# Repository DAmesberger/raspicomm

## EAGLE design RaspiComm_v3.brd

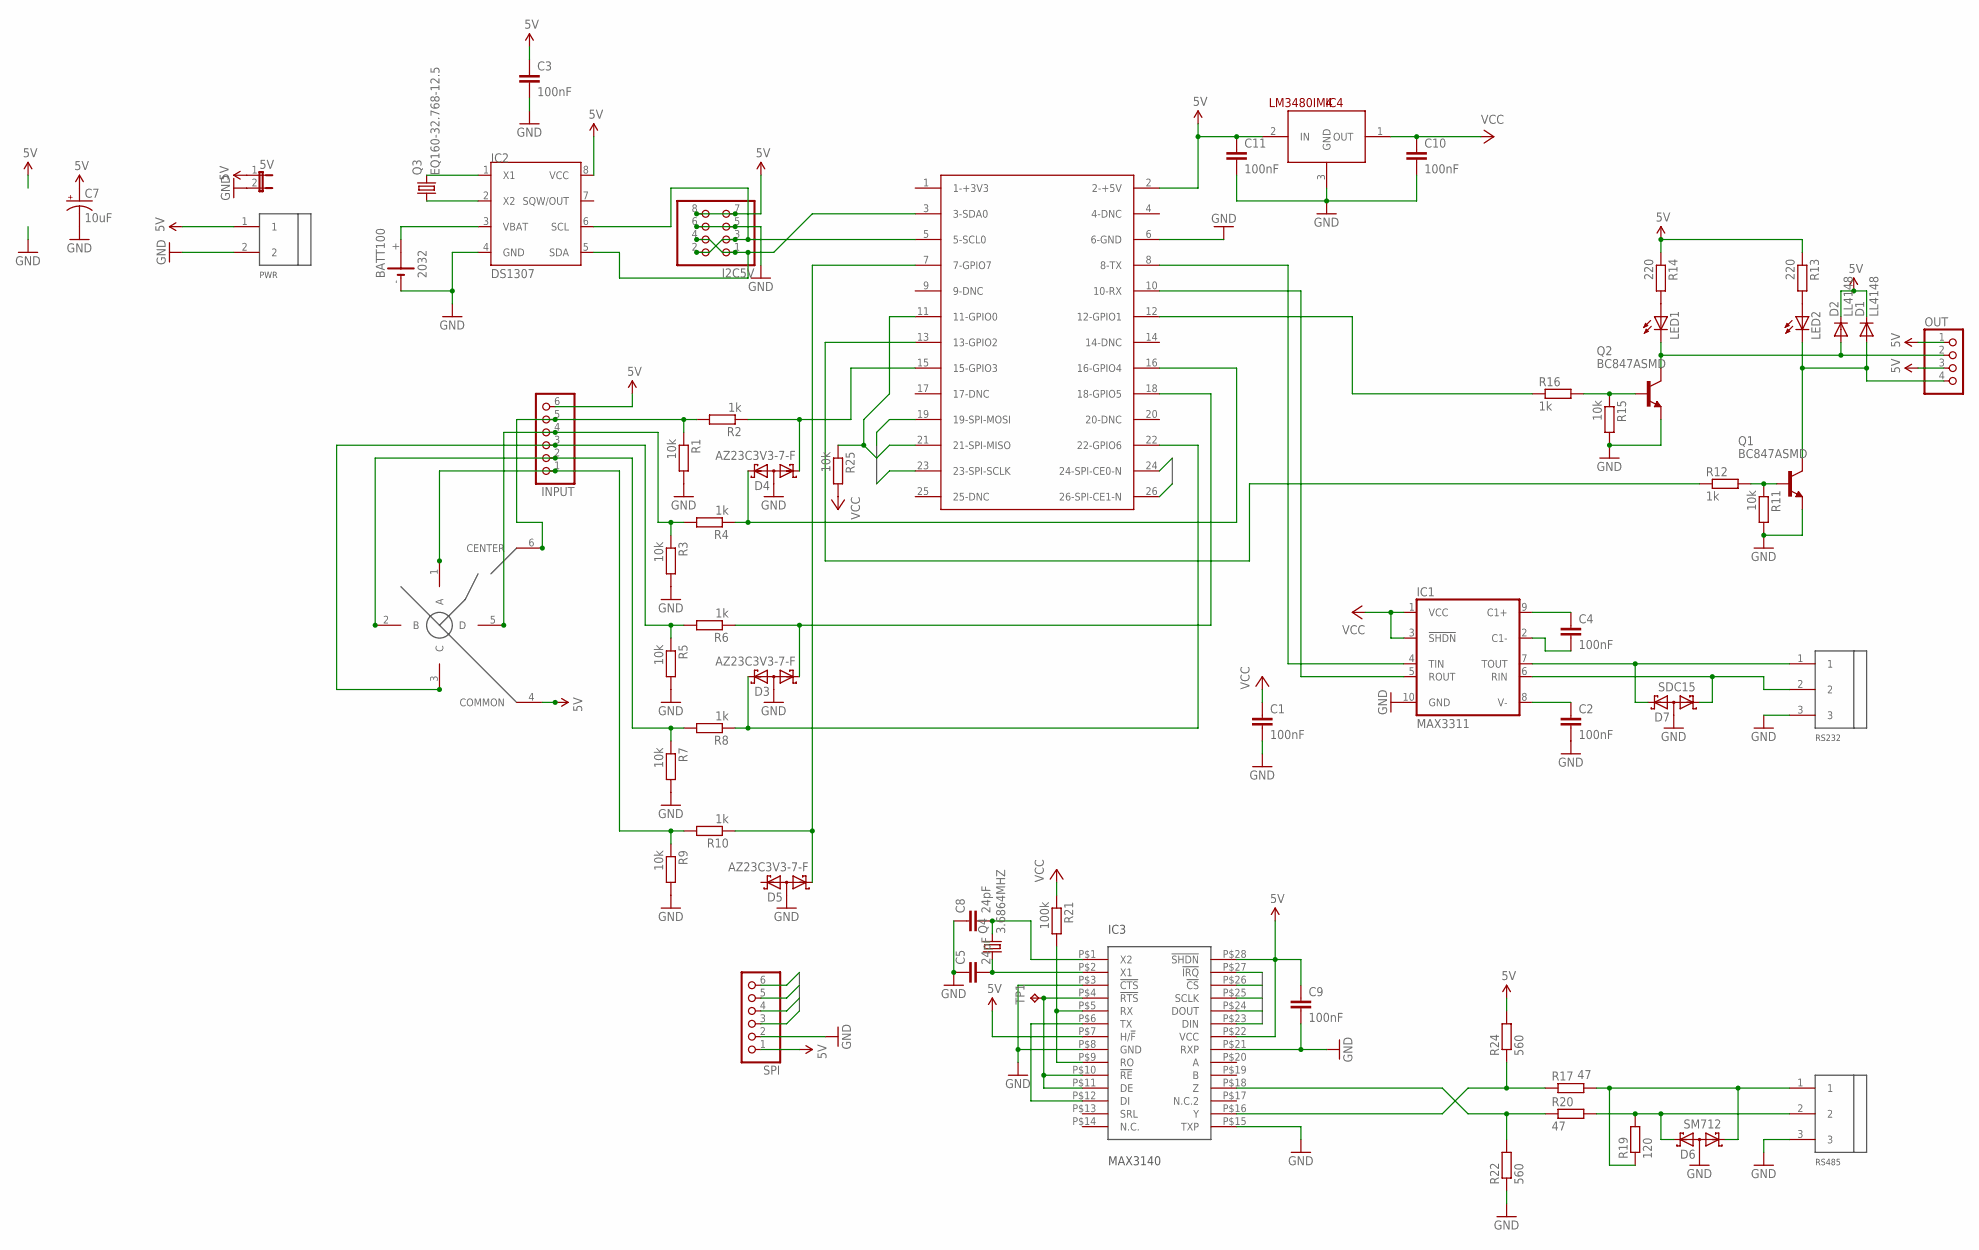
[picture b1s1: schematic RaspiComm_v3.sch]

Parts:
5V: JP1E; JP1
BATT100: 2032; KZH20SMD
C1, C2, C3, C4, C9, C10, C11: 100nF; C0603
C5, C8: 24pF; C0603
C7: 10uF; B(3528-21)
D1, D2: LL4148; SOD80C
D3, D4, D5: AZ23C3V3-7-F; SOT23
D6: SM712; SOT23
D7: SDC15; SOT23
I2C5V: PINHD-2X4_2.54-SMD; 2X04SMD
IC1: MAX3311; UMAX10
IC2: DS1307; SOIC-8
IC3: MAX3140; QSOP28
IC4: LM3480IM4; SOT23-3
INPUT: PINHD-1X6_2.00; 1X06M
LED1, LED2: LEDSML0805; SML0805
OUT: PINHD-1X4_2.00; 1X04M
PWR: 31182102
Q1, Q2: BC847ASMD; SOT23
Q3: EQ160-32.768-12.5; EQ160
Q4: 3.6864MHZ; 49USMX
R1, R3, R5, R7, R9, R11, R15, R25: 10k; R0603
R2, R4, R6, R8, R10, R12, R16: 1k; R0603
R13, R14: 220; R0603
R17, R20: 47; R1206
R19: 120; R1206
R21: 100k; R0603
R22, R24: 560; R0603
RS232, RS485: 31182103
SPI: PINHD-1X6_2.00; 1X06M
SW1: SKQUDBE010; SKQU-SMD
TP1: TPB1,27; B1,27
U$7: RASPBERRY-PIHEADER; RASPI_GPIO_HEADER

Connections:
5V: 5V.1, C3.1, C7.+, C9.1, C11.1, D1.C, D2.C, I2C5V.7, I2C5V.8, IC2.8 (VCC), IC3.P$7 (H/!F), IC3.P$22 (VCC), IC3.P$28 (!SHDN), IC4.2 (IN), INPUT.6, OUT.1, OUT.3, PWR.1, R13.1, R14.1, R24.2, SPI.1, SW1.4 (COMMON), U$7.2 (2-+5V)
CS1: IC3.P$26 (!CS), U$7.24 (24-SPI-CE0-N)
CS2: SPI.3, U$7.26 (26-SPI-CE1-N)
GND: 5V.2, BATT100.-, C1.2, C2.2, C3.2, C5.1, C7.-, C8.1, C9.2, C10.2, C11.2, D3.3 (AA), D4.3 (AA), D5.3 (AA), D6.3 (AA), D7.3 (AA), I2C5V.5, I2C5V.6, IC1.10 (GND), IC2.4 (GND), IC3.P$3 (!CTS), IC3.P$8 (GND), IC3.P$15 (TXP), IC3.P$21 (RXP), IC4.3 (GND), PWR.2, Q1.2 (E), Q2.2 (E), R1.2, R3.2, R5.2, R7.2, R9.2, R11.2, R15.2, R22.1, RS232.3, RS485.3, SPI.2, U$7.6 (6-GND)
IRQ: IC3.P$27 (!IRQ), R25.1, U$7.11 (11-GPIO0)
MISO: IC3.P$24 (DOUT), SPI.5, U$7.21 (21-SPI-MISO)
MOSI: IC3.P$23 (DIN), SPI.6, U$7.19 (19-SPI-MOSI)
unnamed: R16.1, U$7.12 (12-GPIO1)
unnamed: C5.2, IC3.P$2 (X1), Q4.P$1 (1)
unnamed: IC3.P$5 (RX), IC3.P$9 (RO), R21.2
unnamed: IC2.1 (X1), Q3.P$2 (2)
unnamed: IC3.P$16 (Y), R17.1, R24.1
unnamed: IC3.P$18 (Z), R20.1, R22.2
unnamed: I2C5V.2, I2C5V.3, IC2.6 (SCL), U$7.5 (5-SCL0)
unnamed: INPUT.5, R1.1, R2.2, SW1.6 (CENTER)
unnamed: IC3.P$4 (!RTS), IC3.P$10 (!RE), IC3.P$11 (DE), TP1.TP
unnamed: INPUT.4, R3.1, R4.2, SW1.5 (D)
unnamed: INPUT.3, R5.1, R6.2, SW1.3 (C)
unnamed: INPUT.2, R7.1, R8.2, SW1.2 (B)
unnamed: INPUT.1, R9.1, R10.2, SW1.1 (A)
unnamed: D4.1 (K1), R2.1, U$7.15 (15-GPIO3)
unnamed: D4.2 (K2), R4.1, U$7.16 (16-GPIO4)
unnamed: D3.1 (K1), R6.1, U$7.18 (18-GPIO5)
unnamed: D3.2 (K2), R8.1, U$7.22 (22-GPIO6)
unnamed: D5.1 (K1), R10.1, U$7.7 (7-GPIO7)
unnamed: D6.2 (K2), R19.2, R20.2, RS485.2
unnamed: C2.1, IC1.8 (V-)
unnamed: C4.2, IC1.2 (C1-)
unnamed: C4.1, IC1.9 (C1+)
unnamed: D6.1 (K1), R17.2, R19.1, RS485.1
unnamed: LED1.A, R14.2
unnamed: D7.2 (K2), IC1.7 (TOUT), RS232.1
unnamed: D7.1 (K1), IC1.6 (RIN), RS232.2
unnamed: C8.2, IC3.P$1 (X2), Q4.P$2 (2)
unnamed: LED2.A, R13.2
unnamed: D1.A, LED2.C, OUT.4, Q1.3 (C)
unnamed: I2C5V.1, I2C5V.4, IC2.5 (SDA), U$7.3 (3-SDA0)
unnamed: D2.A, LED1.C, OUT.2, Q2.3 (C)
unnamed: IC2.2 (X2), Q3.P$1 (1)
unnamed: Q2.1 (B), R15.1, R16.2
unnamed: Q1.1 (B), R11.1, R12.2
unnamed: BATT100.+, IC2.3 (VBAT)
unnamed: IC3.P$6 (TX), IC3.P$12 (DI)
unnamed: R12.1, U$7.13 (13-GPIO2)
RX: IC1.5 (ROUT), U$7.10 (10-RX)
SCLK: IC3.P$25 (SCLK), SPI.4, U$7.23 (23-SPI-SCLK)
TX: IC1.4 (TIN), U$7.8 (8-TX)
VCC: C1.1, C10.1, IC1.1 (VCC), IC1.3 (!SHDN), IC4.1 (OUT), R21.1, R25.2

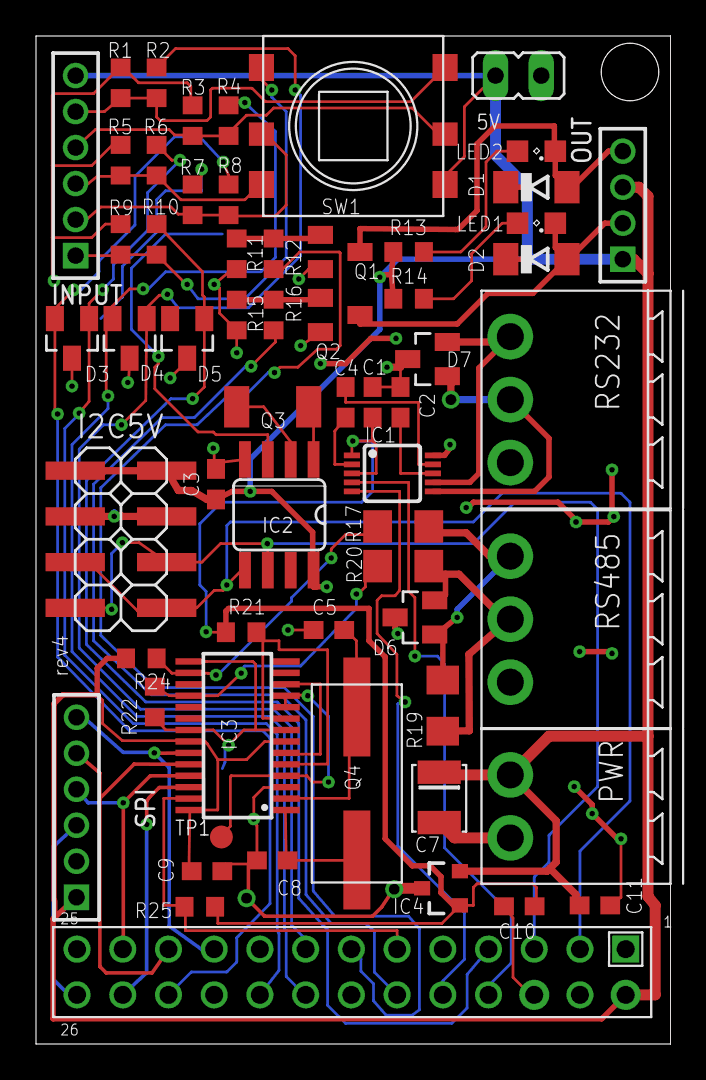
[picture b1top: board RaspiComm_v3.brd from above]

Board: 2 copper layers, 35.2 x 56.0 mm, 62 parts (1 on the bottom side), 48 nets.

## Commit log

2018-06-05 license moved
